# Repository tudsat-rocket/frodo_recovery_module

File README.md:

# Frodo Recovery Module

# Setup

Requires KiCAD version >= 6.0. To generate BOM, install the Interactive HTML BOM plugin: https://github.com/openscopeproject/InteractiveHtmlBom

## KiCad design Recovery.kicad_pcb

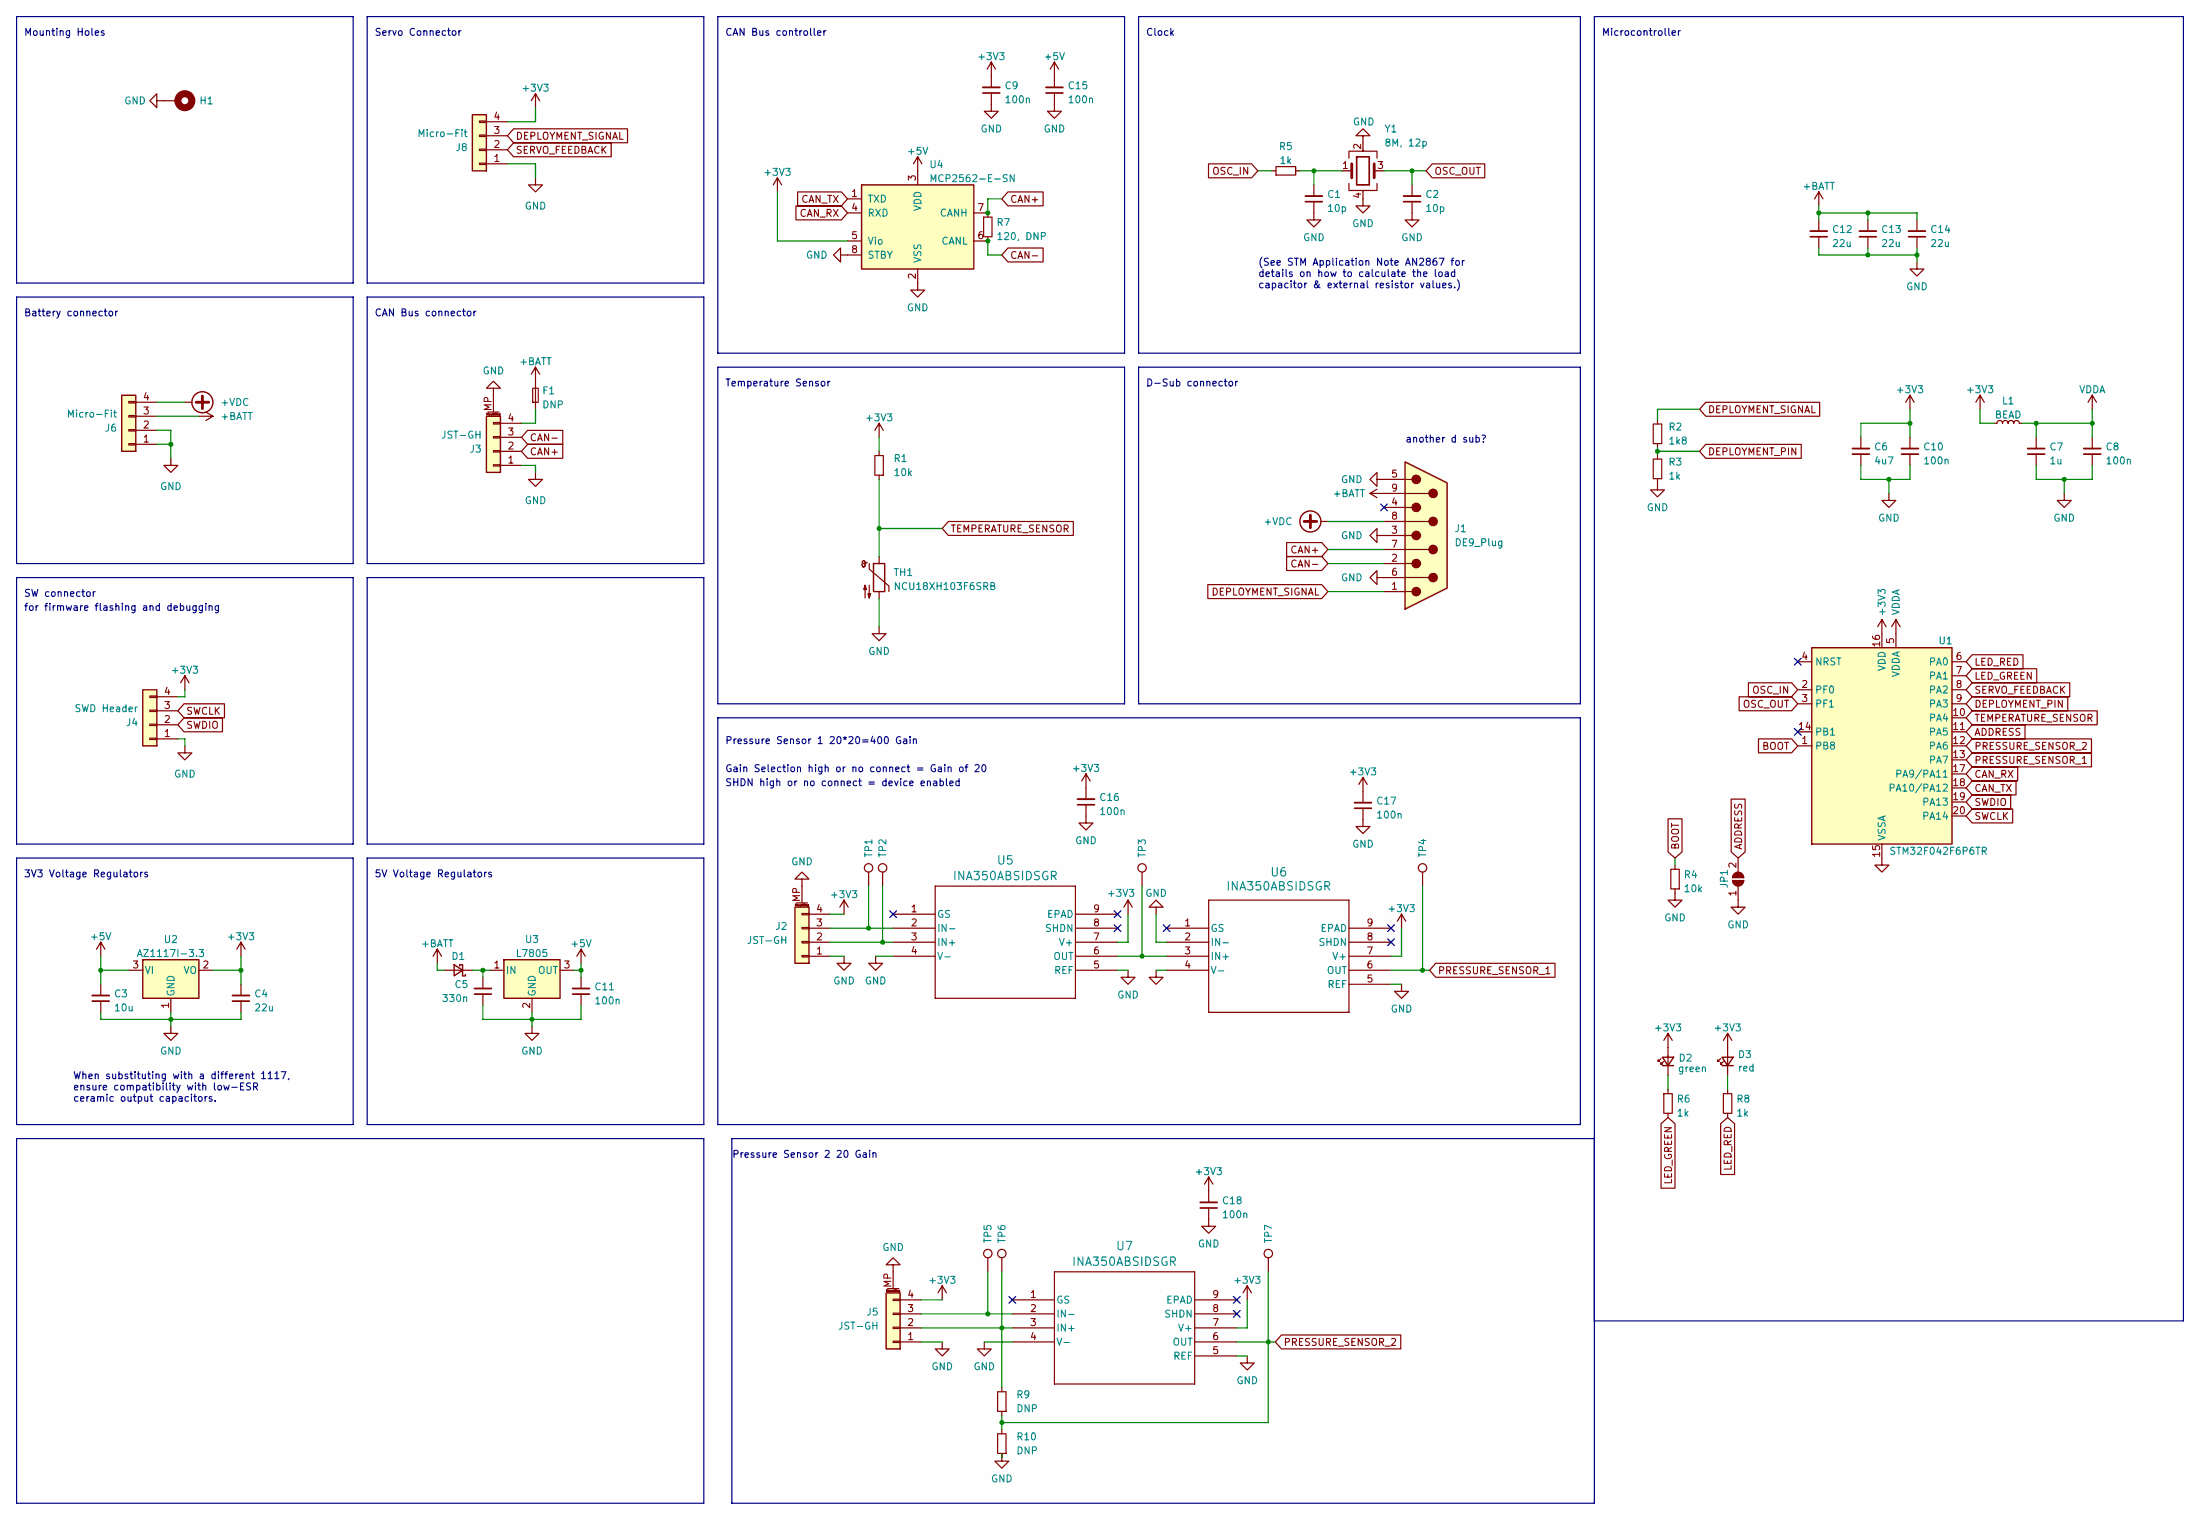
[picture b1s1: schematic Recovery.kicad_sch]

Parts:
C1, C2: 10p; C_0603_1608Metric; Part# CL10C100JB8NNNC; LCSC# C1634
C3: 10u; C_1206_3216Metric; Part# CL31B106KAHNNNE; LCSC# C14860
C4, C12, C13, C14: 22u; C_1206_3216Metric; Part# CL31A226KAHNNNE; LCSC# C12891
C5: 330n; C_0603_1608Metric; Part# CL10B334KO8NNNC; LCSC# C159798
C6: 4u7; C_1206_3216Metric; Part# CL31B475KAHNNNE; LCSC# C1872
C7: 1u; C_0805_2012Metric; Part# CL21A105KBCLNNC; LCSC# C318694
C8, C9, C10, C11, C15, C16, C17, C18: 100n; C_0603_1608Metric; Part# CL10B104KB8NNNC; LCSC# C1591
D1: D_SOD-123F; Part# PMEG3020EH,115; LCSC# C167645
D2: green; LED_0603_1608Metric; Part# 19-217/GHC-YR1S2/3T; LCSC# C72043
D3: red; LED_0603_1608Metric; Part# 19-213/RSC-BS2T2B/3T; LCSC# C474026
F1: DNP; Fuse_1206_3216Metric; Part# N/A; DigiKey# N/A
H1: MountingHole_Pad; MountingHole_2.2mm_M2_Pad; Part# N/A; DigiKey# N/A
J1: DE9_Plug; DSUB-9_Male_Vertical_P2.77x2.84mm_MountingHoles; Part# D09P24A4PL00LF; DigiKey# 609-5545-ND
J2, J3, J5: JST-GH; JST_GH_BM04B-GHS-TBT_1x04-1MP_P1.25mm_Vertical; Part# BM04B-GHS-TBT; LCSC# C161692
J4: SWD Header; PinHeader_1x04_P2.54mm_Vertical; Part# N/A; DigiKey# N/A
J6, J8: Micro-Fit; Molex_Micro-Fit_3.0_43045-0412_2x02_P3.00mm_Vertical; Part# 0430450412; DigiKey# WM1790-ND
JP1: SolderJumper_2_Open; SolderJumper-2_P1.3mm_Open_RoundedPad1.0x1.5mm; Part# N/A; DigiKey# N/A
L1: BEAD; L_0603_1608Metric; Part# BLM18AG601SN1D; LCSC# C19330
R1, R4: 10k; R_0603_1608Metric; Part# RC0603FR-0710KL; LCSC# C98220
R2: 1k8; R_0603_1608Metric; Part# RC0603FR-071K8L; LCSC# C185354
R3, R5, R6, R8: 1k; R_0603_1608Metric; Part# RC0603FR-071KL; LCSC# C22548
R7: 120, DNP; R_0603_1608Metric; Part# RC0603FR-07120RL; LCSC# C114640
R9, R10: DNP; R_0603_1608Metric; Part# N/A; DigiKey# N/A
TH1: NCU18XH103F6SRB; R_0603_1608Metric; Part# NCU18XH103F6SRB; DigiKey# 490-18139-1-ND
TP1, TP2, TP3, TP4, TP5, TP6, TP7: TestPoint; TestPoint_Pad_D2.0mm; Part# N/A; DigiKey# N/A
U1: STM32F042F6P6TR; TSSOP-20_4.4x6.5mm_P0.65mm; Part# STM32F042F6P6TR; DigiKey# 497-19656-1-ND
U2: AZ1117I-3.3; SOT-223-3_TabPin2; Part# AZ1117CH-3.3TRG1; LCSC# C92102
U3: L7805; TO-252-2; Part# L7805CDT-TR; LCSC# C310413
U4: MCP2562-E-SN; SOIC-8_3.9x4.9mm_P1.27mm; Part# MCP2562-H/SN; DigiKey# MCP2562-H/SN
U5, U6, U7: INA350ABSIDSGR; WSON8_DSG_TEX; Part# INA350ABSIDSGR; DigiKey# 296-INA350ABSIDSGRCT-ND
Y1: 8M, 12p; Oscillator_SMD_SeikoEpson_SG210-4Pin_2.5x2.0mm; Part# ECS-80-12-33-JGN-TR; DigiKey# 50-ECS-80-12-33-JGN-CT-ND

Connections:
+3V3: C4.2, C6.2, C9.2, C10.2, C16.2, C17.2, C18.2, D2.2 (A), D3.2 (A), J2.4, J4.4, J5.4, J8.4, L1.1, R1.2, U1.16 (VDD), U2.2 (VO), U4.5 (Vio), U5.7 (V+), U6.7 (V+), U7.7 (V+)
+5V: C3.2, C11.2, C15.2, U2.3 (VI), U3.3 (OUT), U4.3 (VDD)
+BATT: C12.2, C13.2, C14.2, D1.2 (A), F1.2, J1.9, J6.3
+VDC: J1.8, J6.4
ADDRESS: JP1.2 (B), U1.11 (PA5)
BOOT: R4.2, U1.1 (PB8)
CAN+: J1.7, J3.2, R7.1, U4.7 (CANH)
CAN-: J1.2, J3.3, R7.2, U4.6 (CANL)
CAN_RX: U1.17 (PA9/PA11), U4.4 (RXD)
CAN_TX: U1.18 (PA10/PA12), U4.1 (TXD)
DEPLOYMENT_PIN: R2.1, R3.2, U1.9 (PA3)
DEPLOYMENT_SIGNAL: J1.1, J8.3, R2.2
GND: C1.1, C2.1, C3.1, C4.1, C5.1, C6.1, C7.1, C8.1, C9.1, C10.1, C11.1, C12.1, C13.1, C14.1, C15.1, C16.1, C17.1, C18.1, H1.1, J1.3, J1.5, J1.6, J2.1, J2.MP (MountPin), J3.1, J3.MP (MountPin), J4.1, J5.1, J5.MP (MountPin), J6.1, J6.2, J8.1, JP1.1 (A), R3.1, R4.1, R10.1, TH1.2, U1.15 (VSSA), U2.1 (GND), U3.2 (GND), U4.2 (VSS), U4.8 (STBY), U5.4 (V-), U5.5 (REF), U6.2 (IN-), U6.4 (V-), U6.5 (REF), U7.4 (V-), U7.5 (REF), Y1.2, Y1.4
LED_GREEN: R6.2, U1.7 (PA1)
LED_RED: R8.2, U1.6 (PA0)
unnamed: C1.2, R5.2, Y1.1
unnamed: C5.2, D1.1 (K), U3.1 (IN)
unnamed: D2.1 (K), R6.1
unnamed: D3.1 (K), R8.1
unnamed: J2.2, TP2.1, U5.3 (IN+)
unnamed: J2.3, TP1.1, U5.2 (IN-)
unnamed: F1.1, J3.4
unnamed: J5.2, R9.2, TP6.1, U7.3 (IN+)
unnamed: J5.3, TP5.1, U7.2 (IN-)
unnamed: TP3.1, U5.6 (OUT), U6.3 (IN+)
OSC_IN: R5.1, U1.2 (PF0)
OSC_OUT: C2.2, U1.3 (PF1), Y1.3
PRESSURE_SENSOR_1: TP4.1, U1.13 (PA7), U6.6 (OUT)
PRESSURE_SENSOR_2: R9.1, R10.2, TP7.1, U1.12 (PA6), U7.6 (OUT)
SERVO_FEEDBACK: J8.2, U1.8 (PA2)
SWCLK: J4.3, U1.20 (PA14)
SWDIO: J4.2, U1.19 (PA13)
TEMPERATURE_SENSOR: R1.1, TH1.1, U1.10 (PA4)
VDDA: C7.2, C8.2, L1.2, U1.5 (VDDA)

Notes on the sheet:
Pressure Sensor 1 20*20=400 Gain
Battery connector
D-Sub connector
3V3 Voltage Regulators
CAN Bus controller
Servo Connector
Clock
When substituting with a different 1117, ensure compatibility with low-ESR ceramic output capacitors.
Microcontroller
Mounting Holes
for firmware flashing and debugging
SW connector
Temperature Sensor
(See STM Application Note AN2867 for details on how to calculate the load capacitor & external resistor values.)
Pressure Sensor 2 20 Gain
SHDN high or no connect = device enabled
another d sub?
5V Voltage Regulators
CAN Bus connector
Gain Selection high or no connect = Gain of 20

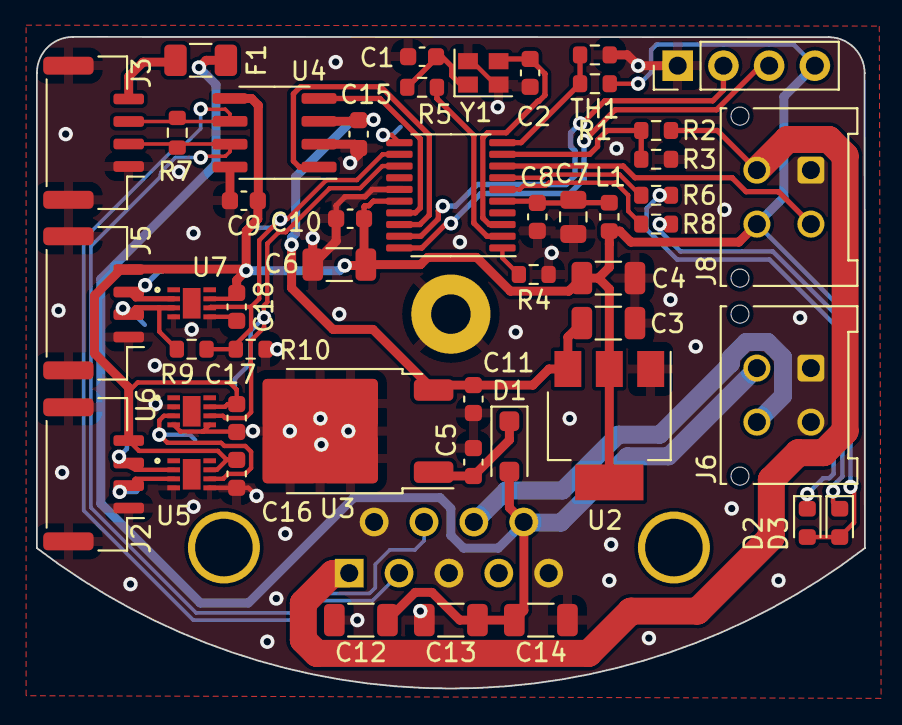
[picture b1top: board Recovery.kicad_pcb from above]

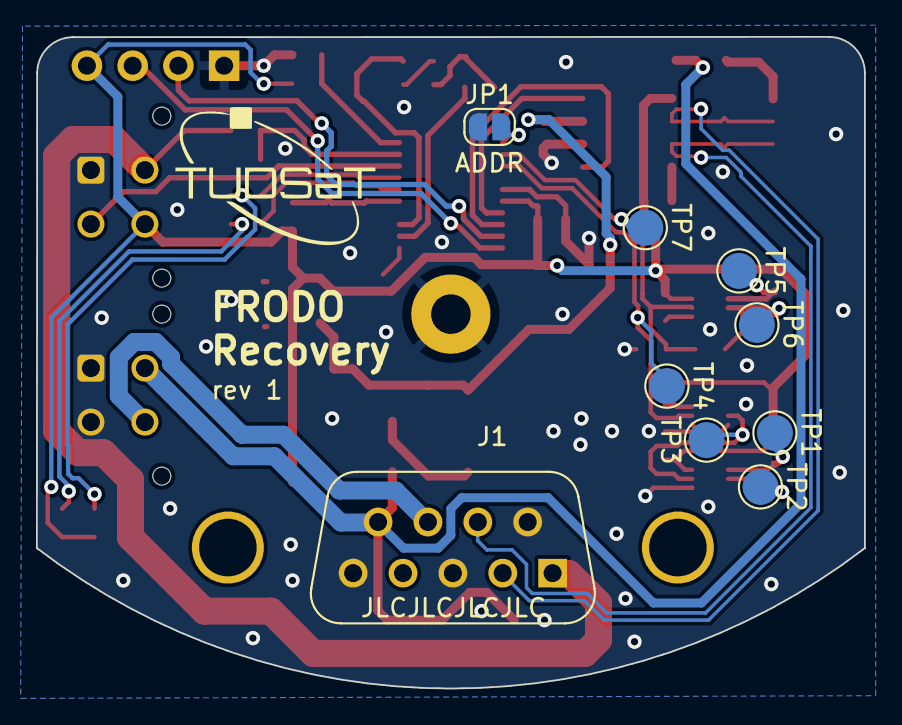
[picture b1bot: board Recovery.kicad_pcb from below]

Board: 2 copper layers, 46.0 x 36.2 mm, 58 parts (9 on the bottom side), 34 nets.

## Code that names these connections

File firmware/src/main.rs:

#![no_std]
#![no_main]
#![feature(type_alias_impl_trait)]

use defmt::*;
use embassy_executor::Spawner;
use embassy_stm32::adc::{Adc, SampleTime};
use embassy_stm32::{bind_interrupts, Config};
use embassy_stm32::can::bxcan::filter::Mask32;
use embassy_stm32::can::bxcan::{Fifo, Frame, StandardId};
use embassy_stm32::can::{Can, Rx0InterruptHandler, Rx1InterruptHandler, SceInterruptHandler, TxInterruptHandler};
use embassy_stm32::gpio::{Input, Pull, Output, Level, Speed};
use embassy_stm32::pac::SYSCFG;
use embassy_stm32::peripherals::CAN;
use embassy_stm32::pac::syscfg::vals::Pa11Pa12Rmp;
use embassy_stm32::time::Hertz;
use embassy_time::{Delay, Duration, Ticker};
use {defmt_rtt as _, panic_probe as _};

bind_interrupts!(struct Irqs {
    CEC_CAN => Rx0InterruptHandler<CAN>, Rx1InterruptHandler<CAN>, SceInterruptHandler<CAN>, TxInterruptHandler<CAN>;
});

#[embassy_executor::main]
async fn main(_spawner: Spawner) {
    let mut config: Config = Default::default();
    config.rcc.hse = Some(Hertz::mhz(8));
    config.rcc.sys_ck = Some(Hertz::mhz(48));

    let p = embassy_stm32::init(config);
    SYSCFG.cfgr1().modify(|w| w.set_pa11_pa12_rmp(Pa11Pa12Rmp::REMAPPED));

    let mut adc = Adc::new(p.ADC, &mut Delay);
    adc.set_sample_time(SampleTime::Cycles239_5);

    let mut vrefint = adc.enable_vref(&mut Delay);
    let vrefint_sample = adc.read_internal(&mut vrefint);
    let convert_to_millivolts = |sample| {
        // From https://www.st.com/resource/en/datasheet/stm32f031c6.pdf
        // 6.3.4 Embedded reference voltage
        const VREFINT_MV: u32 = 1230; // mV

        (u32::from(sample) * VREFINT_MV / u32::from(vrefint_sample)) as u16
    };

    let mut can = Can::new(p.CAN, p.PA11, p.PA12, Irqs);

    can.as_mut()
        .modify_filters()
        .clear();

    can.as_mut()
        .modify_config()
        .set_loopback(false) // Receive own frames
        .set_silent(false)
        .set_automatic_retransmit(false)
        .leave_disabled();

    can.set_bitrate(125_000);

    can.enable().await;

    let _led_red = Output::new(p.PA0, Level::Low, Speed::Low);
    let _led_green = Output::new(p.PA1, Level::Low, Speed::Low);
    let mut ntc = p.PA4;
    let addr = Input::new(p.PA5, Pull::Up);
    let mut pressure_sensor_2 = p.PA6;
    let mut pressure_sensor_1 = p.PA7;

    let can_id = if addr.is_high() { 0x110 } else { 0x111 };

    let mut ticker = Ticker::every(Duration::from_millis(10));
    loop {
        let voltage_sensor_1 = convert_to_millivolts(adc.read(&mut pressure_sensor_1));
        let voltage_sensor_2 = convert_to_millivolts(adc.read(&mut pressure_sensor_2));
        let voltage_ntc = convert_to_millivolts(adc.read(&mut ntc));
        info!("{:03x}, P1: {}mV, P2: {}mV, NTC: {}mV", can_id, voltage_sensor_1, voltage_sensor_2, voltage_ntc);

        let msg = [
            voltage_sensor_1.to_le_bytes()[0],
            voltage_sensor_1.to_le_bytes()[1],
            voltage_sensor_2.to_le_bytes()[0],
            voltage_sensor_2.to_le_bytes()[1],
            voltage_ntc.to_le_bytes()[0],
            voltage_ntc.to_le_bytes()[1],
            0x00,
            0x00
        ];

        let tx_frame = Frame::new_data(unwrap!(StandardId::new(can_id)), msg);
        can.write(&tx_frame).await;

        ticker.next().await;
    }
}

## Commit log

2023-06-09 organise schematic into sections
2023-06-09 fix readme
2023-07-11 update pcb and schematic
2023-07-12 fix pcb size
2023-07-13 finish traces
2023-07-17 Various small fixes
    - increased trace width for deploy signal, removed thermal relief
    - left some room around screw, used pad hole type
    - tweaked CAN traces
    - Added bypass caps to amps, CAN controller
    - Removed 5V rail diode & LED, diode used for BAT instead
    - Used male D-Sub footprint instead of female (affects pin numbering)
2023-10-19 Add firmware to repo
